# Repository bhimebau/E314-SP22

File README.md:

# Spring-2022
Class repository for spring running of embedded systems

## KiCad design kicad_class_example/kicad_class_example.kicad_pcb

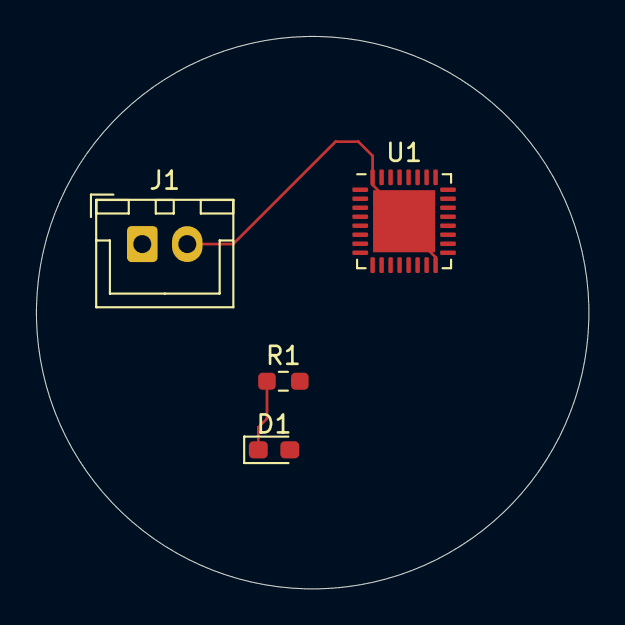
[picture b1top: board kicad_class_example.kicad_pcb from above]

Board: 2 copper layers, 30.7 x 30.7 mm, 4 parts (0 on the bottom side), 4 nets.

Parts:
D1: LED; LED_0603_1608Metric_Pad1.05x0.95mm_HandSolder
J1: Conn_01x02_Male; JST_XH_B2B-XH-A_1x02_P2.50mm_Vertical
R1: 470; R_0603_1608Metric_Pad0.98x0.95mm_HandSolder
U1: STM32L432KCUx; QFN-32-1EP_5x5mm_P0.5mm_EP3.45x3.45mm

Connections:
+3V3: D1.2, J1.1, U1.1, U1.5, U1.17
GND: J1.2, U1.16, U1.32, U1.33
unnamed: D1.1, R1.1
unnamed: R1.2, U1.6

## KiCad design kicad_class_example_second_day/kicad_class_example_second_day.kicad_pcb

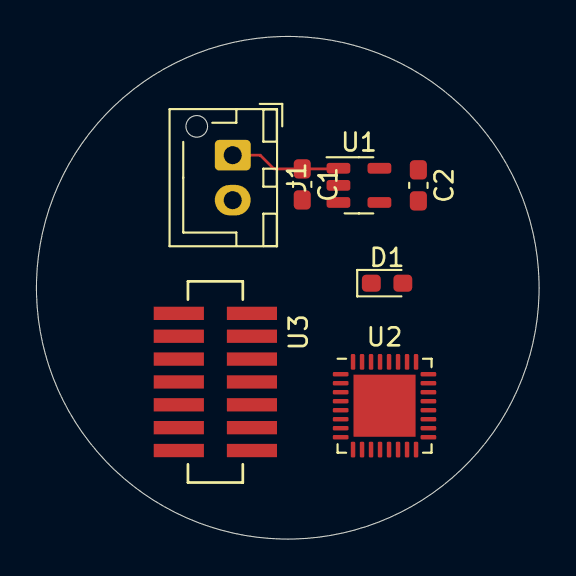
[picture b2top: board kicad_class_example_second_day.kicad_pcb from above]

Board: 2 copper layers, 27.9 x 27.9 mm, 8 parts (1 on the bottom side), 11 nets.

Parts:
C1, C2: 1uF; C_0603_1608Metric_Pad1.08x0.95mm_HandSolder
D1: LED; LED_0603_1608Metric_Pad1.05x0.95mm_HandSolder
J1: Conn_01x02_Male; JST_XH_B2B-XH-AM_1x02_P2.50mm_Vertical
R1: 470; R_0603_1608Metric_Pad0.98x0.95mm_HandSolder
U1: TPS76933; SOT-23-5
U2: STM32L432KCUx; QFN-32-1EP_5x5mm_P0.5mm_EP3.45x3.45mm
U3: STDC14; ftsh_14p_connector

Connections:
+3V3: C2.1, R1.1, U1.5, U2.1, U2.5, U2.17, U3.3
/reset: U2.4, U3.12
/rx: U2.9, U3.14
/swclk: U2.24, U3.6
/swdio: U2.23, U3.4
/swo: U2.26, U3.8
/tx: U2.8, U3.13
GND: C1.2, C2.2, J1.2, U1.2, U1.3, U2.16, U2.32, U2.33, U3.5, U3.7, U3.11
unnamed: C1.1, J1.1, U1.1
unnamed: D1.1, U2.6
unnamed: D1.2, R1.2

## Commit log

2021-12-17 pulled from spring 2021
2022-01-07 removed all files that represented using a command line approach
2022-01-07 corrected README
2022-01-20 added embedded systems code
2022-01-24 added the debugging source code
2022-01-24 added openocd binaries
2022-02-01 removed openocd from the top level
2022-02-01 added example uart code
2022-02-21 added an example for the sensors
2022-02-25 removed internal lab6 example
2022-02-25 removed build directory
2022-02-25 cleanup
2022-02-25 pre scaled ADC to correct L412 issue
2022-03-02 added the kicad libraries
2022-03-09 corrected symbol library issue
2022-04-15 added the light sensor code
2022-04-15 corrected openocd link
